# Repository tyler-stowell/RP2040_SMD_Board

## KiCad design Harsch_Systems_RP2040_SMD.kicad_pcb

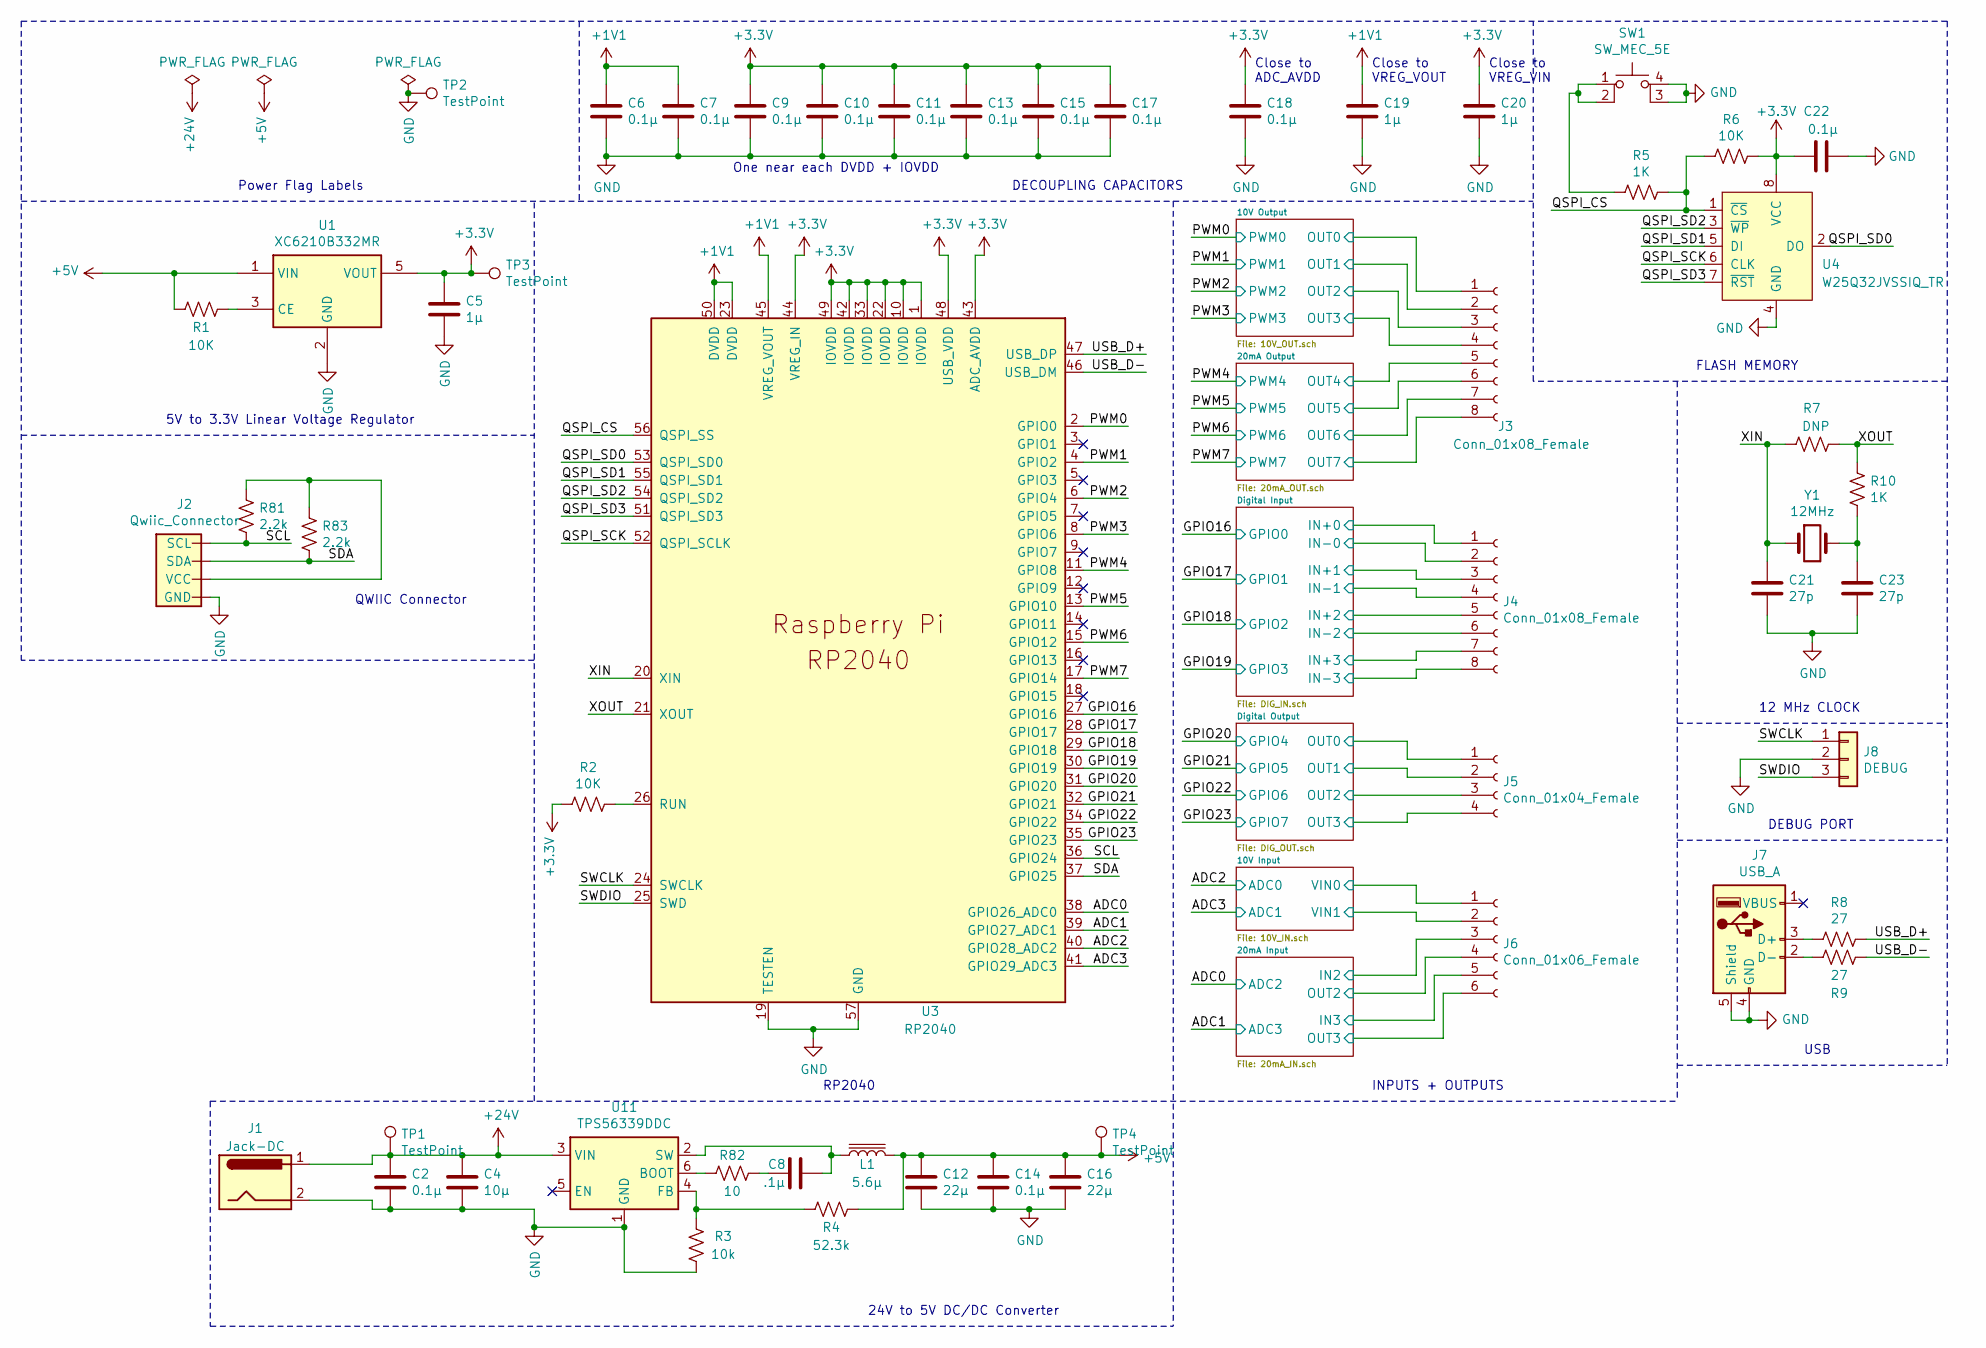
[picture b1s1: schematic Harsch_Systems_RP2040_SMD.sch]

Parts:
C2, C6, C7, C9, C10, C11, C13, C14, C15, C17, C18, C22: 0.1μ; C_0603_1608Metric
C4: 10μ; C_0805_2012Metric
C5: 1μ; C_0805_2012Metric
C8: .1μ; C_0805_2012Metric
C12, C16: 22μ; C_0805_2012Metric
C19, C20: 1μ; C_0603_1608Metric
C21, C23: 27p; C_0805_2012Metric
J1: Jack-DC; BarrelJack_Horizontal
J2: Qwiic_Connector; 1X04_1MM_RA
J3, J4: Conn_01x08_Female; PinHeader_1x08_P2.54mm_Vertical
J5: Conn_01x04_Female; PinHeader_1x04_P2.54mm_Vertical
J6: Conn_01x06_Female; PinHeader_1x06_P2.54mm_Vertical
J7: USB_A; USB_Micro-B_GCT_USB3076-30-A
J8: DEBUG; PinHeader_1x03_P2.54mm_Vertical
L1: 5.6μ; L_Vishay_IHLP-2020
R1, R2, R6: 10K; R_0805_2012Metric
R3: 10k; R_0805_2012Metric
R4: 52.3k; R_0805_2012Metric
R5, R10: 1K; R_0805_2012Metric
R7: DNP; R_0805_2012Metric
R8, R9: 27; R_0805_2012Metric
R81, R83: 2.2k; R_0805_2012Metric
R82: 10; R_0805_2012Metric
SW1: SW_MEC_5E; SW_SPST_Omron_B3FS-100xP
TP1, TP2, TP3, TP4: TestPoint; PinSocket_1x01_P2.54mm_Vertical
U1: XC6210B332MR; SOT-23-5
U3: RP2040; RP2040-QFN-56
U4: W25Q32JVSSIQ_TR; SOIC-8_W5.6mm; MPN W25Q32JVSSIQ TR; Digi-Key_PN W25Q32JVSSIQCT-ND
U11: TPS56339DDC; SOT-23-6
Y1: 12MHz; Crystal_SMD_0603-2Pin_6.0x3.5mm

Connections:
+1V1: C6.1, C7.1, C19.1, U3.23 (DVDD), U3.45 (VREG_VOUT), U3.50 (DVDD)
+3V3: C5.1, C9.1, C10.1, C11.1, C13.1, C15.1, C17.1, C18.1, C20.1, C22.1, R2.2, R6.1, TP3.1, U1.5 (VOUT), U3.1 (IOVDD), U3.10 (IOVDD), U3.22 (IOVDD), U3.33 (IOVDD), U3.42 (IOVDD), U3.43 (ADC_AVDD), U3.44 (VREG_IN), U3.48 (USB_VDD), U3.49 (IOVDD), U4.8 (VCC); also elsewhere on the board
+5V: C12.1, C14.1, C16.1, L1.2, R1.2, R4.2, TP4.1, U1.1 (VIN); also elsewhere on the board
+24V: C2.1, C4.1, J1.1, TP1.1, U11.3 (VIN); also elsewhere on the board
/10V Input/VIN0: J6.1; also elsewhere on the board
/10V Input/VIN1: J6.2; also elsewhere on the board
/10V Output/OUT0: J3.1; also elsewhere on the board
/10V Output/OUT1: J3.2; also elsewhere on the board
/10V Output/OUT2: J3.3; also elsewhere on the board
/10V Output/OUT3: J3.4; also elsewhere on the board
/20mA Input/IN2: J6.3; also elsewhere on the board
/20mA Input/IN3: J6.5; also elsewhere on the board
/20mA Input/OUT2: J6.4; also elsewhere on the board
/20mA Input/OUT3: J6.6; also elsewhere on the board
/20mA Output/OUT4: J3.5; also elsewhere on the board
/20mA Output/OUT5: J3.6; also elsewhere on the board
/20mA Output/OUT6: J3.7; also elsewhere on the board
/20mA Output/OUT7: J3.8; also elsewhere on the board
/ADC0: U3.38 (GPIO26_ADC0); also elsewhere on the board
/ADC1: U3.39 (GPIO27_ADC1); also elsewhere on the board
/ADC2: U3.40 (GPIO28_ADC2); also elsewhere on the board
/ADC3: U3.41 (GPIO29_ADC3); also elsewhere on the board
/Digital Input/IN+0: J4.1; also elsewhere on the board
/Digital Input/IN+1: J4.3; also elsewhere on the board
/Digital Input/IN+2: J4.5; also elsewhere on the board
/Digital Input/IN+3: J4.7; also elsewhere on the board
/Digital Input/IN-0: J4.2; also elsewhere on the board
/Digital Input/IN-1: J4.4; also elsewhere on the board
/Digital Input/IN-2: J4.6; also elsewhere on the board
/Digital Input/IN-3: J4.8; also elsewhere on the board
/Digital Output/OUT0: J5.1; also elsewhere on the board
/Digital Output/OUT1: J5.2; also elsewhere on the board
/Digital Output/OUT2: J5.3; also elsewhere on the board
/Digital Output/OUT3: J5.4; also elsewhere on the board
/GPIO16: U3.27 (GPIO16); also elsewhere on the board
/GPIO17: U3.28 (GPIO17); also elsewhere on the board
/GPIO18: U3.29 (GPIO18); also elsewhere on the board
/GPIO19: U3.30 (GPIO19); also elsewhere on the board
/GPIO20: U3.31 (GPIO20); also elsewhere on the board
/GPIO21: U3.32 (GPIO21); also elsewhere on the board
/GPIO22: U3.34 (GPIO22); also elsewhere on the board
/GPIO23: U3.35 (GPIO23); also elsewhere on the board
/PWM0: U3.2 (GPIO0); also elsewhere on the board
/PWM1: U3.4 (GPIO2); also elsewhere on the board
/PWM2: U3.6 (GPIO4); also elsewhere on the board
/PWM3: U3.8 (GPIO6); also elsewhere on the board
/PWM4: U3.11 (GPIO8); also elsewhere on the board
/PWM5: U3.13 (GPIO10); also elsewhere on the board
/PWM6: U3.15 (GPIO12); also elsewhere on the board
/PWM7: U3.17 (GPIO14); also elsewhere on the board
/QSPI_CS: R5.1, R6.2, U3.56 (QSPI_SS), U4.1 (~CS)
/QSPI_SCK: U3.52 (QSPI_SCLK), U4.6 (CLK)
/QSPI_SD0: U3.53 (QSPI_SD0), U4.2 (DO)
/QSPI_SD1: U3.55 (QSPI_SD1), U4.5 (DI)
/QSPI_SD2: U3.54 (QSPI_SD2), U4.3 (~WP)
/QSPI_SD3: U3.51 (QSPI_SD3), U4.7 (~RST)
/SCL: J2.4 (SCL), R81.2, U3.36 (GPIO24)
/SDA: J2.3 (SDA), R83.2, U3.37 (GPIO25)
/SWCLK: J8.1, U3.24 (SWCLK)
/SWDIO: J8.3, U3.25 (SWD)
/USB_D+: R8.1, U3.47 (USB_DP)
/USB_D-: R9.1, U3.46 (USB_DM)
/XIN: C21.1, R7.1, U3.20 (XIN), Y1.1
/XOUT: R7.2, R10.1, U3.21 (XOUT)
GND: C2.2, C4.2, C5.2, C6.2, C7.2, C9.2, C10.2, C11.2, C12.2, C13.2, C14.2, C15.2, C16.2, C17.2, C18.2, C19.2, C20.2, C21.2, C22.2, C23.2, J1.2, J2.1 (GND), J7.4 (GND), J7.5 (Shield), J8.2, R3.1, SW1.3 (K), SW1.4 (A), TP2.1, U1.2 (GND), U3.19 (TESTEN), U3.57 (GND), U4.4 (GND), U11.1 (GND); also elsewhere on the board
unnamed: C8.1, R82.1
unnamed: C8.2, L1.1, U11.2 (SW)
unnamed: C23.1, R10.2, Y1.2
unnamed: J2.2 (VCC), R81.1, R83.1
unnamed: J7.2 (D-), R9.2
unnamed: J7.3 (D+), R8.2
unnamed: R1.1, U1.3 (CE)
unnamed: R2.1, U3.26 (RUN)
unnamed: R3.2, R4.1, U11.4 (FB)
unnamed: R5.2, SW1.1, SW1.2
unnamed: R82.2, U11.6 (BOOT)

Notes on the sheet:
One near each DVDD + IOVDD
Close to ADC_AVDD
Close to VREG_VOUT
Close to VREG_VIN
DEBUG PORT
12 MHz CLOCK
FLASH MEMORY
USB
INPUTS + OUTPUTS
DECOUPLING CAPACITORS
RP2040
24V to 5V DC/DC Converter
Power Flag Labels
5V to 3.3V Linear Voltage Regulator
QWIIC Connector

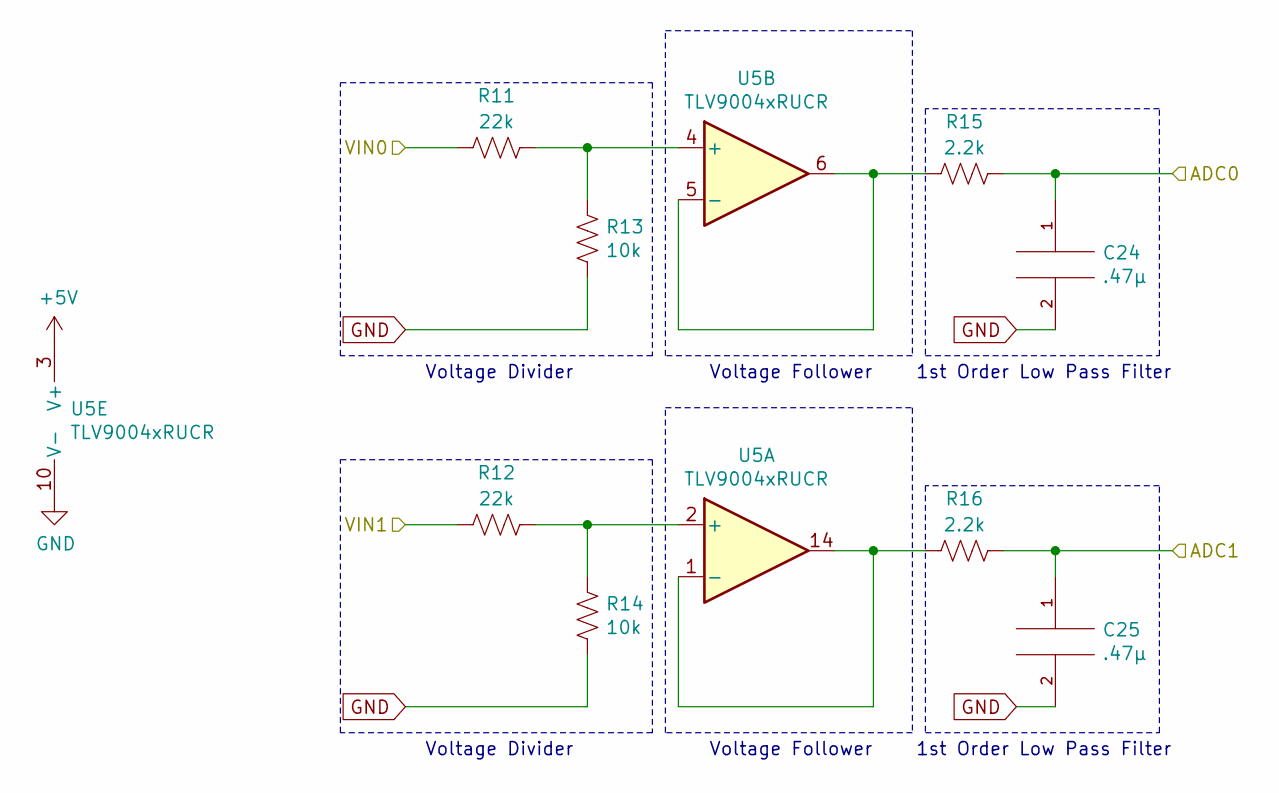
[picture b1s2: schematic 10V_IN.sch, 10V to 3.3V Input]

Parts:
C24, C25: .47μ; C_0805_2012Metric
R11, R12: 22k; R_0805_2012Metric
R13, R14: 10k; R_0805_2012Metric
R15, R16: 2.2k; R_0805_2012Metric
U5: TLV9004xRUCR; SOIC-14_3.9x8.7mm_P1.27mm

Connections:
+5V: U5.3 (V+); also elsewhere on the board
/10V Input/VIN0: R11.2; also elsewhere on the board
/10V Input/VIN1: R12.2; also elsewhere on the board
/ADC2: C24.1, R15.1; also elsewhere on the board
/ADC3: C25.1, R16.1; also elsewhere on the board
GND: C24.2, C25.2, R13.1, R14.1, U5.10 (V-); also elsewhere on the board
unnamed: R11.1, R13.2, U5.4 (+)
unnamed: R12.1, R14.2, U5.2 (+)
unnamed: R15.2, U5.5 (-), U5.6
unnamed: R16.2, U5.1 (-), U5.14

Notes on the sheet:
Voltage Divider
Voltage Follower
1st Order Low Pass Filter

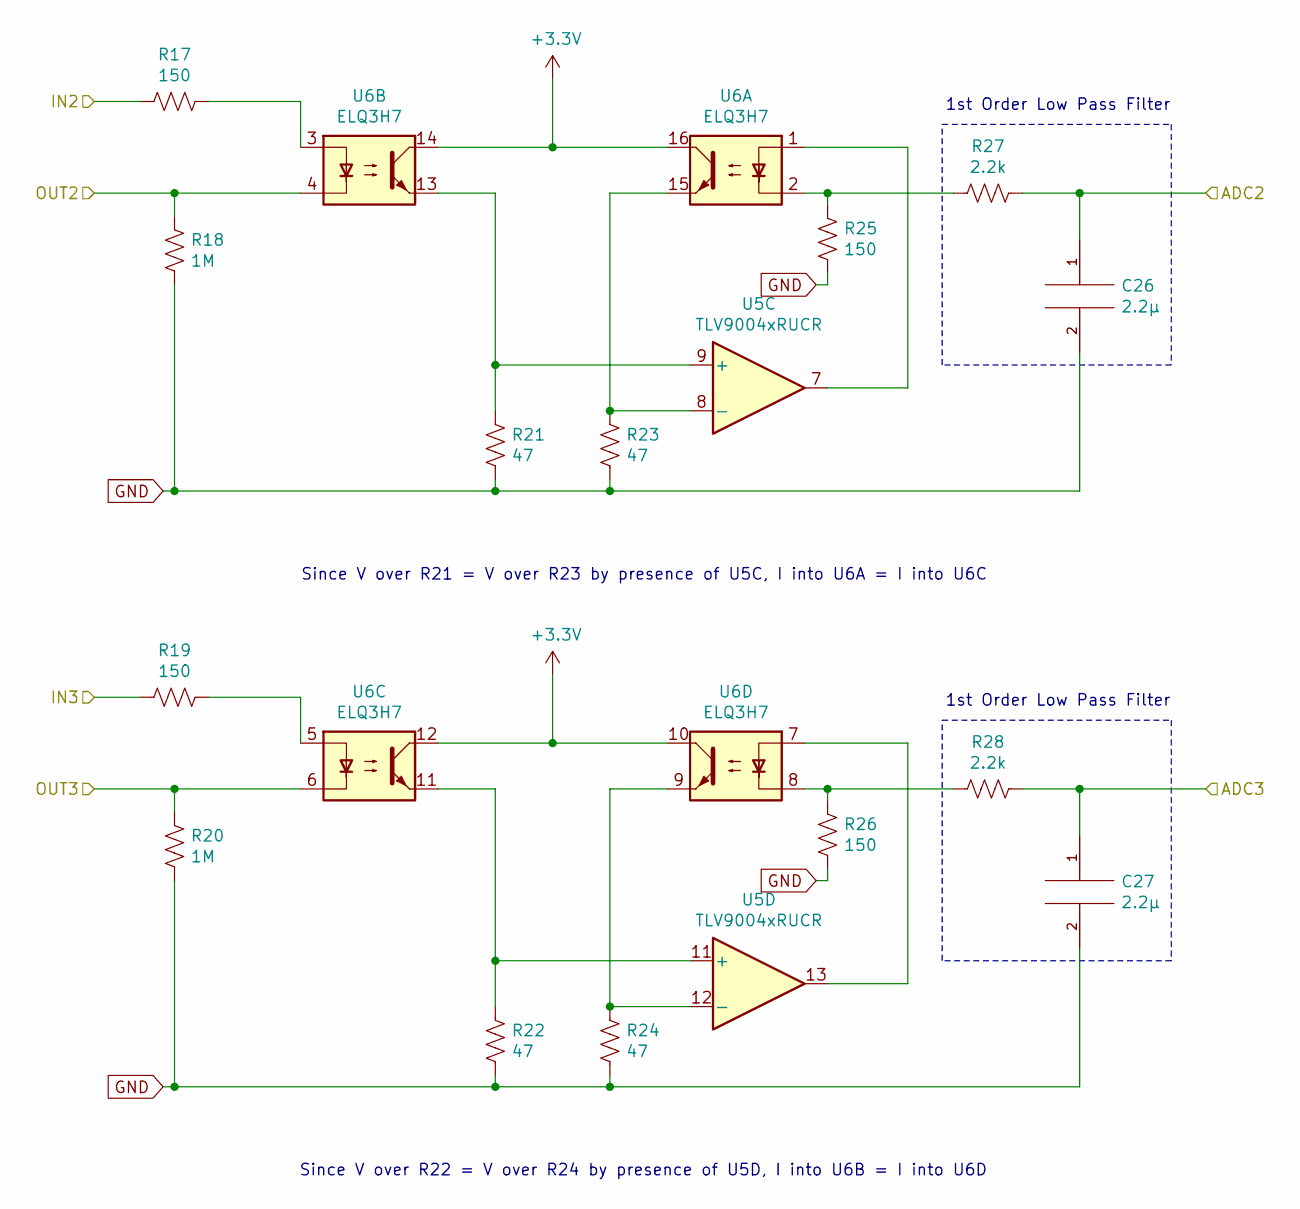
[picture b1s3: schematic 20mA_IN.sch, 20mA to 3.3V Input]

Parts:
C26, C27: 2.2µ; C_0805_2012Metric
R17, R19, R25, R26: 150; R_0805_2012Metric
R18, R20: 1M; R_0805_2012Metric
R21, R22, R23, R24: 47; R_1210_3225Metric
R27, R28: 2.2k; R_0805_2012Metric
U5: TLV9004xRUCR; SOIC-14_3.9x8.7mm_P1.27mm
U6: ELQ3H7; SOP-16_3.9x9.9mm_P1.27mm

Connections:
+3V3: U6.10, U6.12, U6.14, U6.16; also elsewhere on the board
/20mA Input/IN2: R17.2; also elsewhere on the board
/20mA Input/IN3: R19.2; also elsewhere on the board
/20mA Input/OUT2: R18.2, U6.4; also elsewhere on the board
/20mA Input/OUT3: R20.2, U6.6; also elsewhere on the board
/ADC0: C26.1, R27.1; also elsewhere on the board
/ADC1: C27.1, R28.1; also elsewhere on the board
GND: C26.2, C27.2, R18.1, R20.1, R21.1, R22.1, R23.1, R24.1, R25.1, R26.1; also elsewhere on the board
unnamed: R17.1, U6.3
unnamed: R19.1, U6.5
unnamed: R21.2, U5.9 (+), U6.13
unnamed: R22.2, U5.11 (+), U6.11
unnamed: R23.2, U5.8 (-), U6.15
unnamed: R24.2, U5.12 (-), U6.9
unnamed: R25.2, R27.2, U6.2
unnamed: R26.2, R28.2, U6.8
unnamed: U5.7, U6.1
unnamed: U5.13, U6.7

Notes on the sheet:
1st Order Low Pass Filter
Since V over R22 = V over R24 by presence of U5D, I into U6B = I into U6D
Since V over R21 = V over R23 by presence of U5C, I into U6A = I into U6C

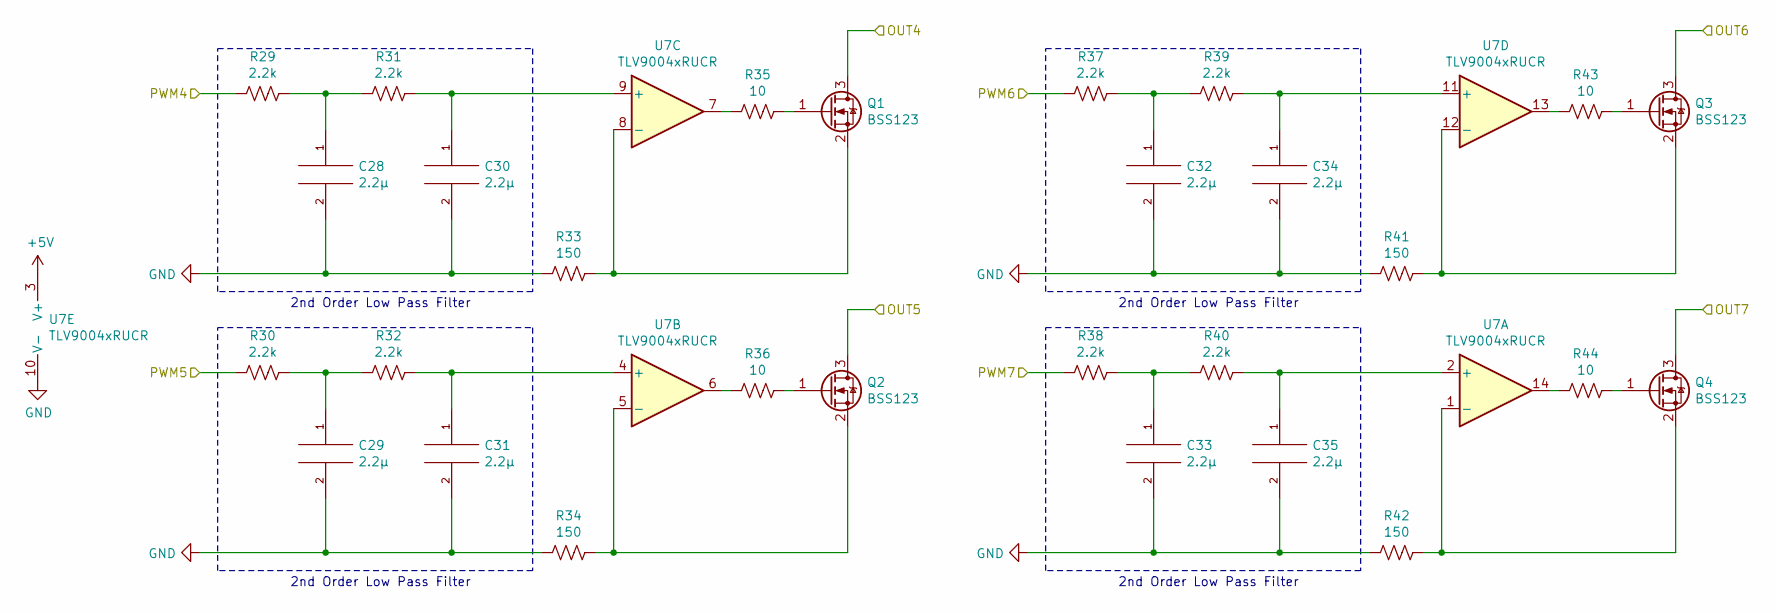
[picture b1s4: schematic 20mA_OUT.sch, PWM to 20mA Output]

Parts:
C28, C29, C30, C31, C32, C33, C34, C35: 2.2μ; C_0805_2012Metric
Q1, Q2, Q3, Q4: BSS123; SOT-23
R29, R30, R31, R32, R37, R38, R39, R40: 2.2k; R_0805_2012Metric
R33, R34, R41, R42: 150; R_0805_2012Metric
R35, R36, R43, R44: 10; R_0805_2012Metric
U7: TLV9004xRUCR; SOIC-14_3.9x8.7mm_P1.27mm

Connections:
+5V: U7.3 (V+); also elsewhere on the board
/20mA Output/OUT4: Q1.3 (D); also elsewhere on the board
/20mA Output/OUT5: Q2.3 (D); also elsewhere on the board
/20mA Output/OUT6: Q3.3 (D); also elsewhere on the board
/20mA Output/OUT7: Q4.3 (D); also elsewhere on the board
/PWM4: R29.2; also elsewhere on the board
/PWM5: R30.2; also elsewhere on the board
/PWM6: R37.2; also elsewhere on the board
/PWM7: R38.2; also elsewhere on the board
GND: C28.2, C29.2, C30.2, C31.2, C32.2, C33.2, C34.2, C35.2, R33.2, R34.2, R41.2, R42.2, U7.10 (V-); also elsewhere on the board
unnamed: C28.1, R29.1, R31.2
unnamed: C29.1, R30.1, R32.2
unnamed: C30.1, R31.1, U7.9 (+)
unnamed: C31.1, R32.1, U7.4 (+)
unnamed: C32.1, R37.1, R39.2
unnamed: C33.1, R38.1, R40.2
unnamed: C34.1, R39.1, U7.11 (+)
unnamed: C35.1, R40.1, U7.2 (+)
unnamed: Q1.1 (G), R35.1
unnamed: Q1.2 (S), R33.1, U7.8 (-)
unnamed: Q2.1 (G), R36.1
unnamed: Q2.2 (S), R34.1, U7.5 (-)
unnamed: Q3.1 (G), R43.1
unnamed: Q3.2 (S), R41.1, U7.12 (-)
unnamed: Q4.1 (G), R44.1
unnamed: Q4.2 (S), R42.1, U7.1 (-)
unnamed: R35.2, U7.7
unnamed: R36.2, U7.6
unnamed: R43.2, U7.13
unnamed: R44.2, U7.14

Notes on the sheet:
2nd Order Low Pass Filter

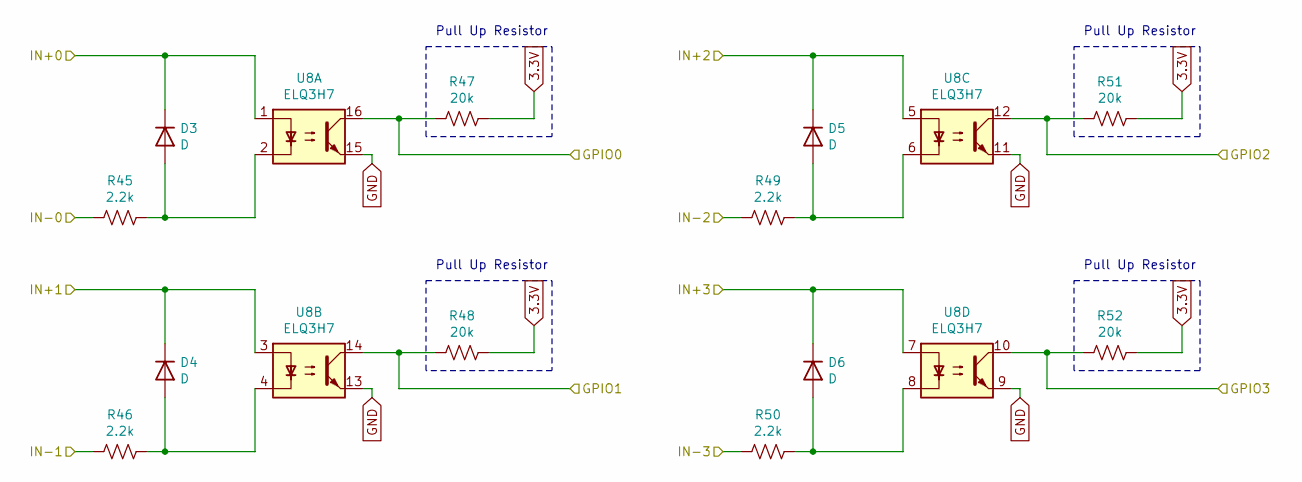
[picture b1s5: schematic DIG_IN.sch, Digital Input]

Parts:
D3, D4, D5, D6: D; D_0805_2012Metric
R45, R46, R49, R50: 2.2k; R_1210_3225Metric
R47, R48, R51, R52: 20k; R_0805_2012Metric
U8: ELQ3H7; SOP-16_3.9x9.9mm_P1.27mm

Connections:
3.3V: R47.1, R48.1, R51.1, R52.1
/Digital Input/IN+0: D3.1 (K), U8.1; also elsewhere on the board
/Digital Input/IN+1: D4.1 (K), U8.3; also elsewhere on the board
/Digital Input/IN+2: D5.1 (K), U8.5; also elsewhere on the board
/Digital Input/IN+3: D6.1 (K), U8.7; also elsewhere on the board
/Digital Input/IN-0: R45.1; also elsewhere on the board
/Digital Input/IN-1: R46.1; also elsewhere on the board
/Digital Input/IN-2: R49.1; also elsewhere on the board
/Digital Input/IN-3: R50.1; also elsewhere on the board
/GPIO16: R47.2, U8.16; also elsewhere on the board
/GPIO17: R48.2, U8.14; also elsewhere on the board
/GPIO18: R51.2, U8.12; also elsewhere on the board
/GPIO19: R52.2, U8.10; also elsewhere on the board
GND: U8.9, U8.11, U8.13, U8.15; also elsewhere on the board
unnamed: D3.2 (A), R45.2, U8.2
unnamed: D4.2 (A), R46.2, U8.4
unnamed: D5.2 (A), R49.2, U8.6
unnamed: D6.2 (A), R50.2, U8.8

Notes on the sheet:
Pull Up Resistor

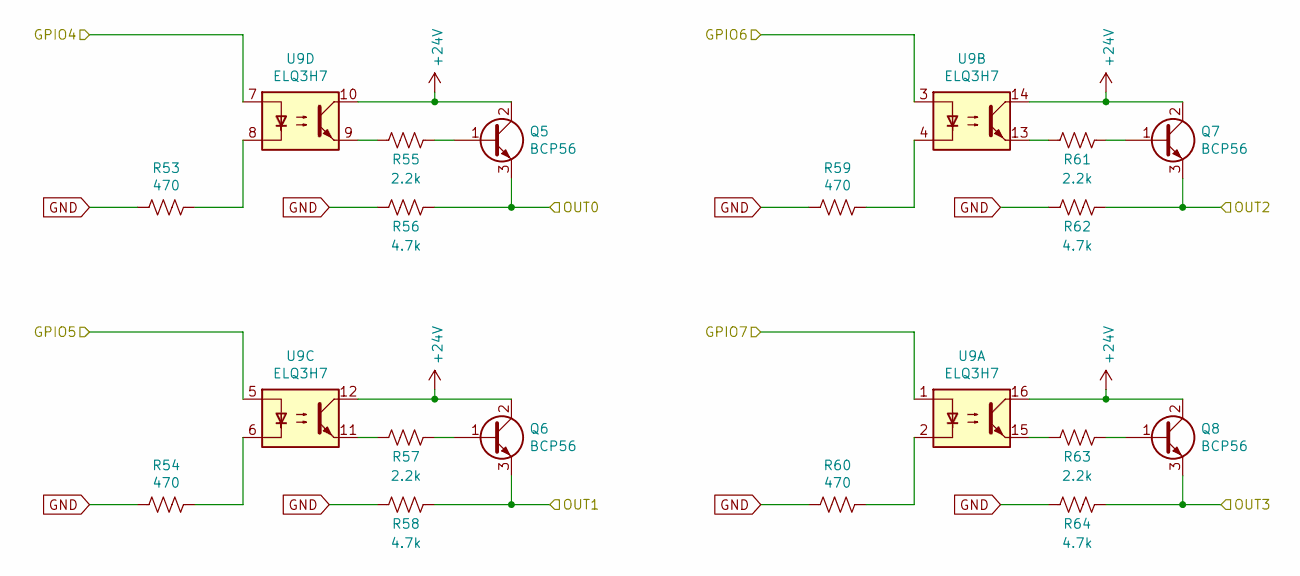
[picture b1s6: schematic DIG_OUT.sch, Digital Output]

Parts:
Q5, Q6, Q7, Q8: BCP56; SOT-223
R53, R54, R59, R60: 470; R_0805_2012Metric
R55, R57, R61, R63: 2.2k; R_0805_2012Metric
R56, R58, R62, R64: 4.7k; R_0805_2012Metric
U9: ELQ3H7; SOP-16_3.9x9.9mm_P1.27mm

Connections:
+24V: Q5.2 (C), Q5.4 (C), Q6.2 (C), Q6.4 (C), Q7.2 (C), Q7.4 (C), Q8.2 (C), Q8.4 (C), U9.10, U9.12, U9.14, U9.16; also elsewhere on the board
/Digital Output/OUT0: Q5.3 (E), R56.2; also elsewhere on the board
/Digital Output/OUT1: Q6.3 (E), R58.2; also elsewhere on the board
/Digital Output/OUT2: Q7.3 (E), R62.2; also elsewhere on the board
/Digital Output/OUT3: Q8.3 (E), R64.2; also elsewhere on the board
/GPIO20: U9.7; also elsewhere on the board
/GPIO21: U9.5; also elsewhere on the board
/GPIO22: U9.3; also elsewhere on the board
/GPIO23: U9.1; also elsewhere on the board
GND: R53.1, R54.1, R56.1, R58.1, R59.1, R60.1, R62.1, R64.1; also elsewhere on the board
unnamed: Q5.1 (B), R55.2
unnamed: Q6.1 (B), R57.2
unnamed: Q7.1 (B), R61.2
unnamed: Q8.1 (B), R63.2
unnamed: R53.2, U9.8
unnamed: R54.2, U9.6
unnamed: R55.1, U9.9
unnamed: R57.1, U9.11
unnamed: R59.2, U9.4
unnamed: R60.2, U9.2
unnamed: R61.1, U9.13
unnamed: R63.1, U9.15

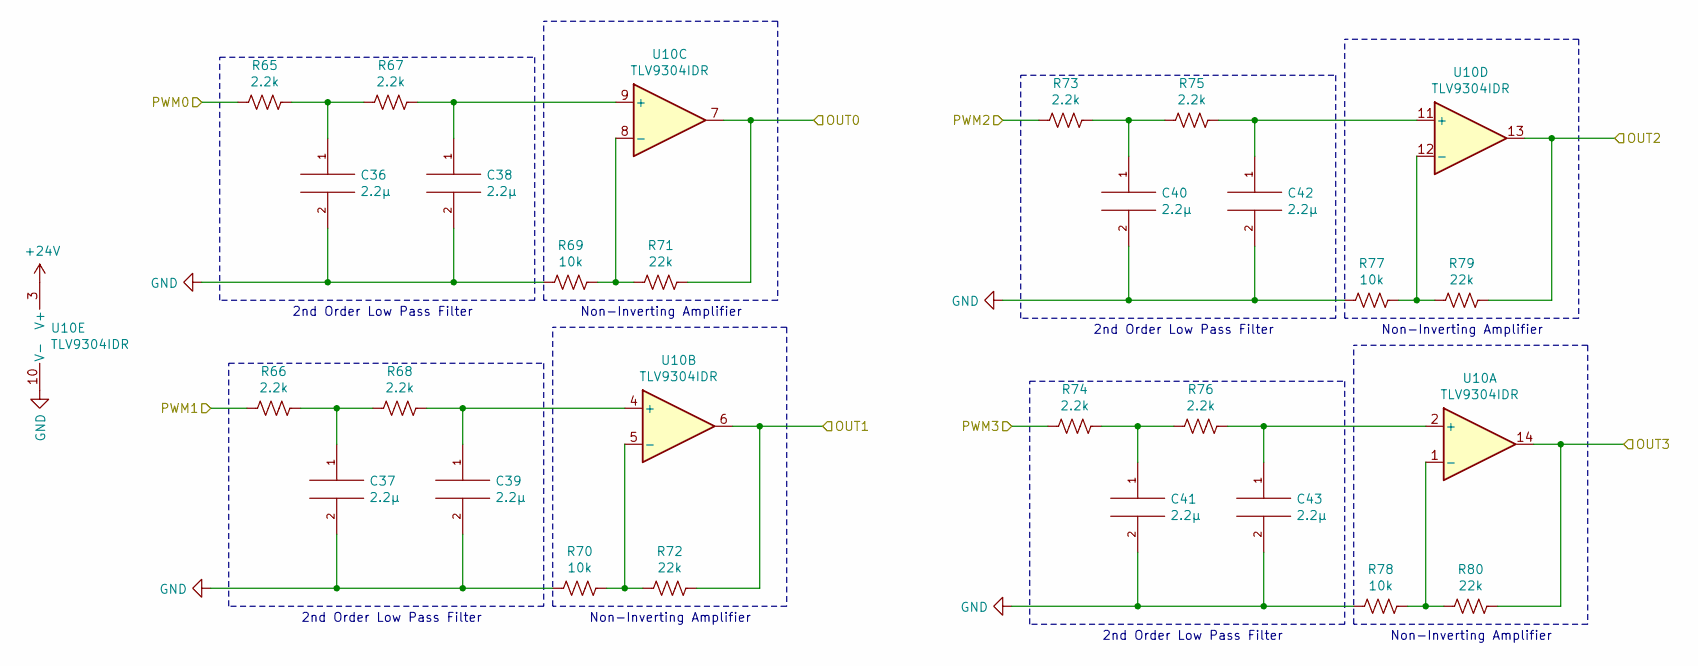
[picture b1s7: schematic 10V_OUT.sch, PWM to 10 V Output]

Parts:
C36, C37, C38, C39, C40, C41, C42, C43: 2.2μ; C_0805_2012Metric
R65, R66, R67, R68, R73, R74, R75, R76: 2.2k; R_0805_2012Metric
R69, R70, R77, R78: 10k; R_0805_2012Metric
R71, R72, R79, R80: 22k; R_0805_2012Metric
U10: TLV9304IDR; SOIC-14_3.9x8.7mm_P1.27mm

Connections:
+24V: U10.3 (V+); also elsewhere on the board
/10V Output/OUT0: R71.1, U10.7; also elsewhere on the board
/10V Output/OUT1: R72.1, U10.6; also elsewhere on the board
/10V Output/OUT2: R79.1, U10.13; also elsewhere on the board
/10V Output/OUT3: R80.1, U10.14; also elsewhere on the board
/PWM0: R65.2; also elsewhere on the board
/PWM1: R66.2; also elsewhere on the board
/PWM2: R73.2; also elsewhere on the board
/PWM3: R74.2; also elsewhere on the board
GND: C36.2, C37.2, C38.2, C39.2, C40.2, C41.2, C42.2, C43.2, R69.2, R70.2, R77.2, R78.2, U10.10 (V-); also elsewhere on the board
unnamed: C36.1, R65.1, R67.2
unnamed: C37.1, R66.1, R68.2
unnamed: C38.1, R67.1, U10.9 (+)
unnamed: C39.1, R68.1, U10.4 (+)
unnamed: C40.1, R73.1, R75.2
unnamed: C41.1, R74.1, R76.2
unnamed: C42.1, R75.1, U10.11 (+)
unnamed: C43.1, R76.1, U10.2 (+)
unnamed: R69.1, R71.2, U10.8 (-)
unnamed: R70.1, R72.2, U10.5 (-)
unnamed: R77.1, R79.2, U10.12 (-)
unnamed: R78.1, R80.2, U10.1 (-)

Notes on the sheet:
2nd Order Low Pass Filter
Non-Inverting Amplifier

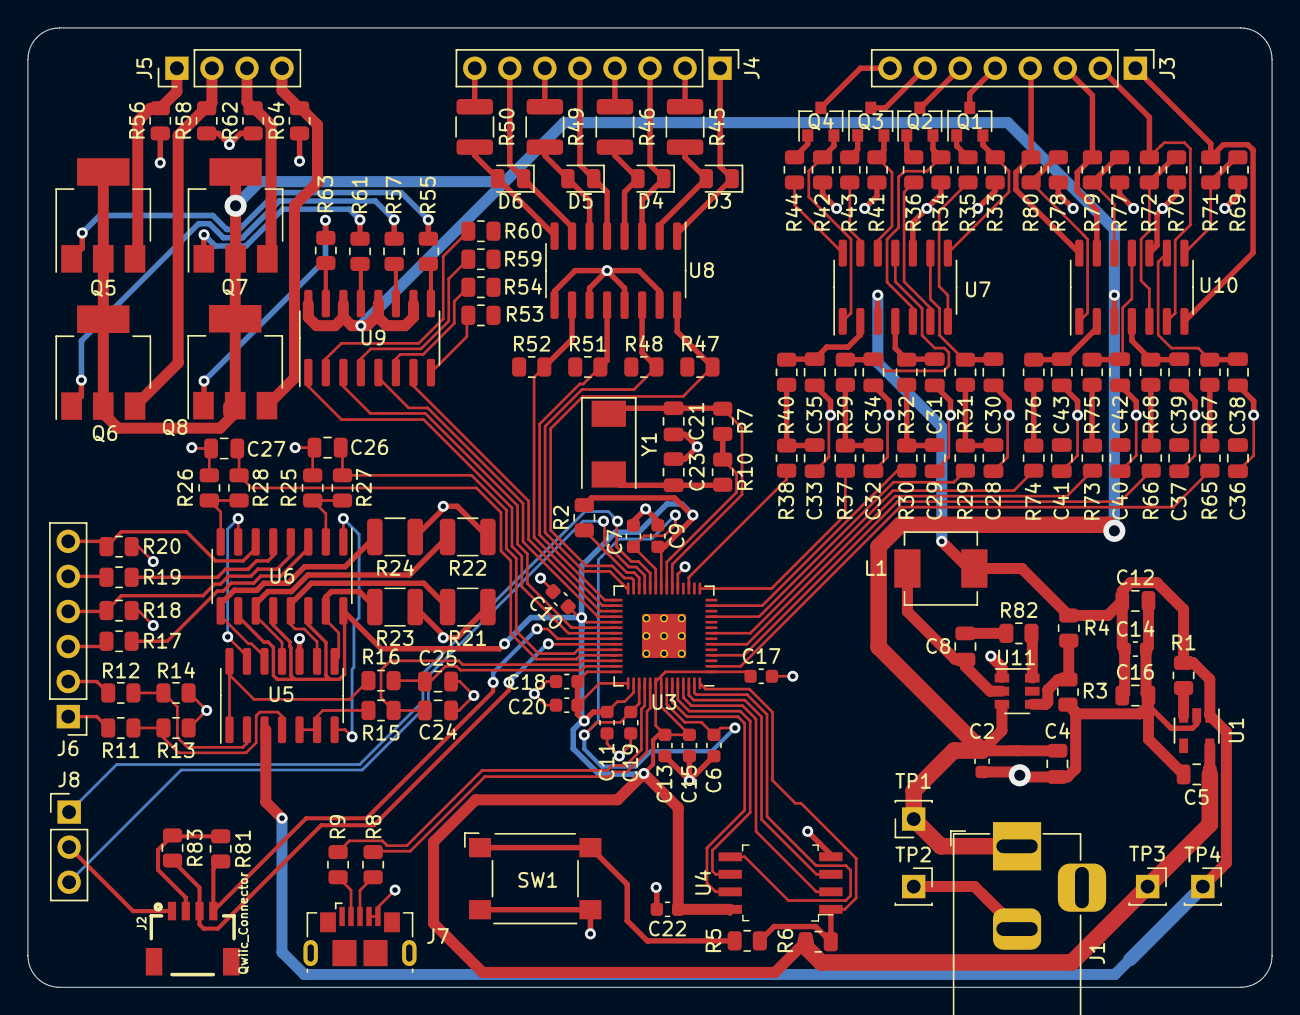
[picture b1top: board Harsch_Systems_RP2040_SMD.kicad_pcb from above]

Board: 2 copper layers, 90.2 x 69.5 mm, 161 parts (0 on the bottom side), 139 nets.

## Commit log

2021-07-19 Initial commit of SMD based RP2040 industrial board
2021-07-22 Updates, cleanup, and component association.
2021-07-23 Starting routing
2021-07-24 Finished the schematic, except for maybe a couple test points.
2021-08-04 Routing for all analog outputs
2021-08-05 Routed ADC inputs and adjusted some trace widths
2021-08-05 Power circuitry routing and board outline
2021-08-06 Everything but the 24V output is routed
2021-08-06 Finished routing, but realized an optocoupler on 24V outputs isn't rated high enough
2021-08-06 Re-added mounting holes, fixed a small issue
2021-08-09 Adjusted some tracks and vias for better heat dissipation
2021-08-09 Added an I2C QWIIC Connector
